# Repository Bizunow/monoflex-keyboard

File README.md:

# Monoflex keyboard

This repo contains case, plate, foam and PCB  design files for a Monoflex keyboard.

Case, plates and foam designed by me ([Bizunow](https://github.com/Bizunow)) and PCB designed by [keyten](https://github.com/KeyTen1).

Maintained by [Bizunow](https://github.com/Bizunow) & [ILWrites](https://github.com/pikeeb)

QMK Firmware source available on ILWrites' [Monoflex QMK branch](https://github.com/PiKeeb/qmk_firmware/tree/monoflex/keyboards/monoflex60)

Huge thanks to all, who helped me design this keyboard.

Licenced under WTFPL v2

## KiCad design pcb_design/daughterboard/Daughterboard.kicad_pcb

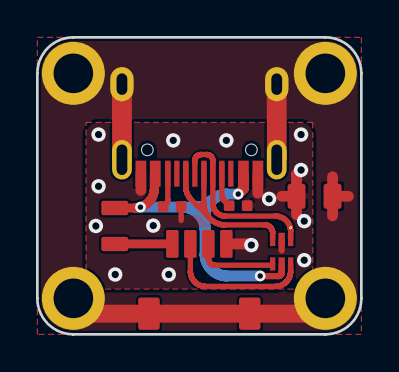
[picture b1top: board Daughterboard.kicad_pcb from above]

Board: 2 copper layers, 18.0 x 16.5 mm, 11 parts (0 on the bottom side), 10 nets.

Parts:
F1: 350mA; Fuse_0805
J1: TYPE-C-31-M12_13; TYPE-C-31-M-12
J2: JST SH; JST_SH
J3, J4, J5, J6: Conn_01x01; M2_MountingHole
L1: 60Ω@100MHz; L_0805
R1, R2: 5.1kΩ; R_0402
U2: USBLC6-2P6; SOT-666

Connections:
+5V: F1.2, J2.1
D+: J2.3, U2.4
D-: J2.2, U2.6
DBUS+: J1.A6, J1.B6, U2.3
DBUS-: J1.A7, J1.B7, U2.1
GND: J1.A1, J1.B1, J2.4, L1.2, R1.2, R2.1, U2.2
GNDPWR: J1.S, J2.5, J2.6, J3.1, J4.1, J5.1, J6.1, L1.1
unnamed: J1.A5, R1.1
unnamed: J1.B5, R2.2
VBUS: F1.1, J1.A4, J1.B4, U2.5

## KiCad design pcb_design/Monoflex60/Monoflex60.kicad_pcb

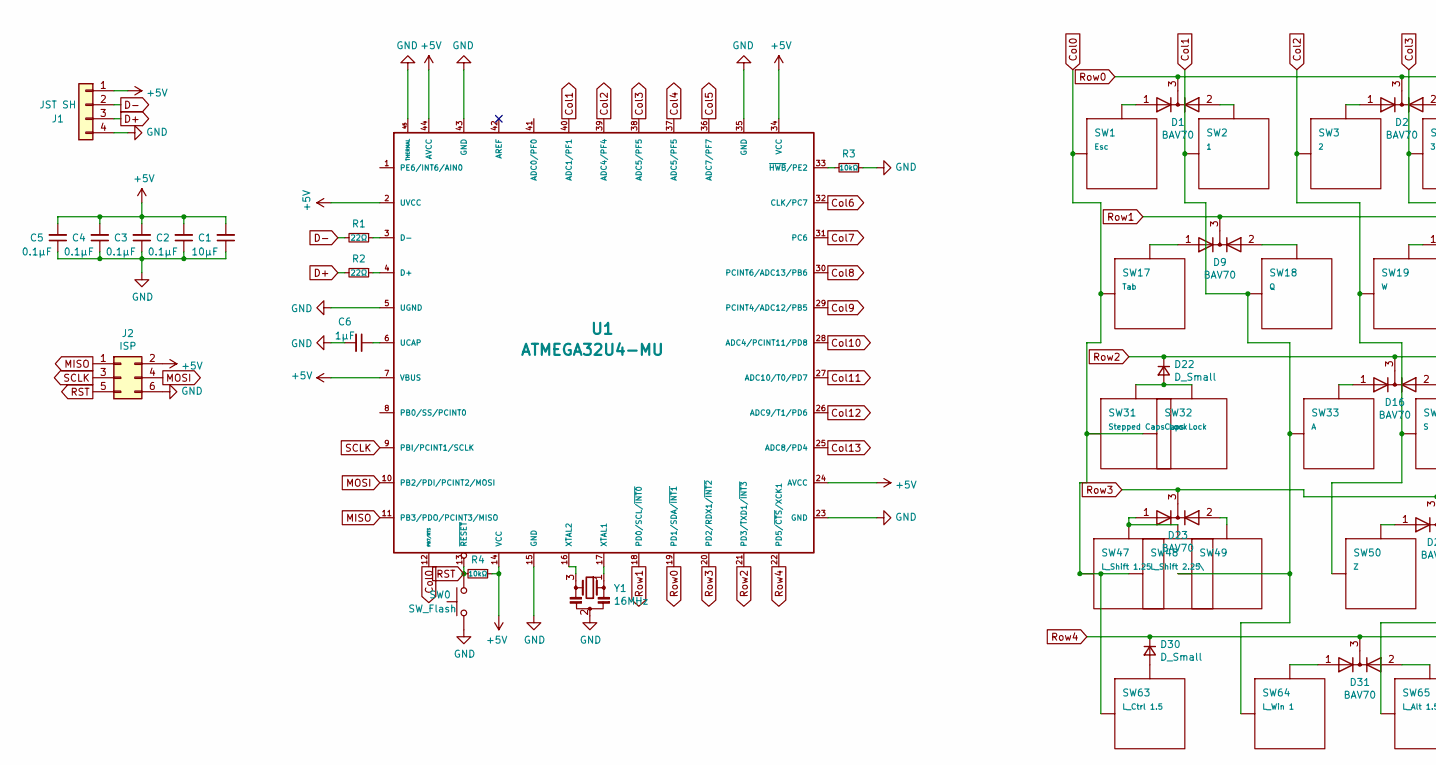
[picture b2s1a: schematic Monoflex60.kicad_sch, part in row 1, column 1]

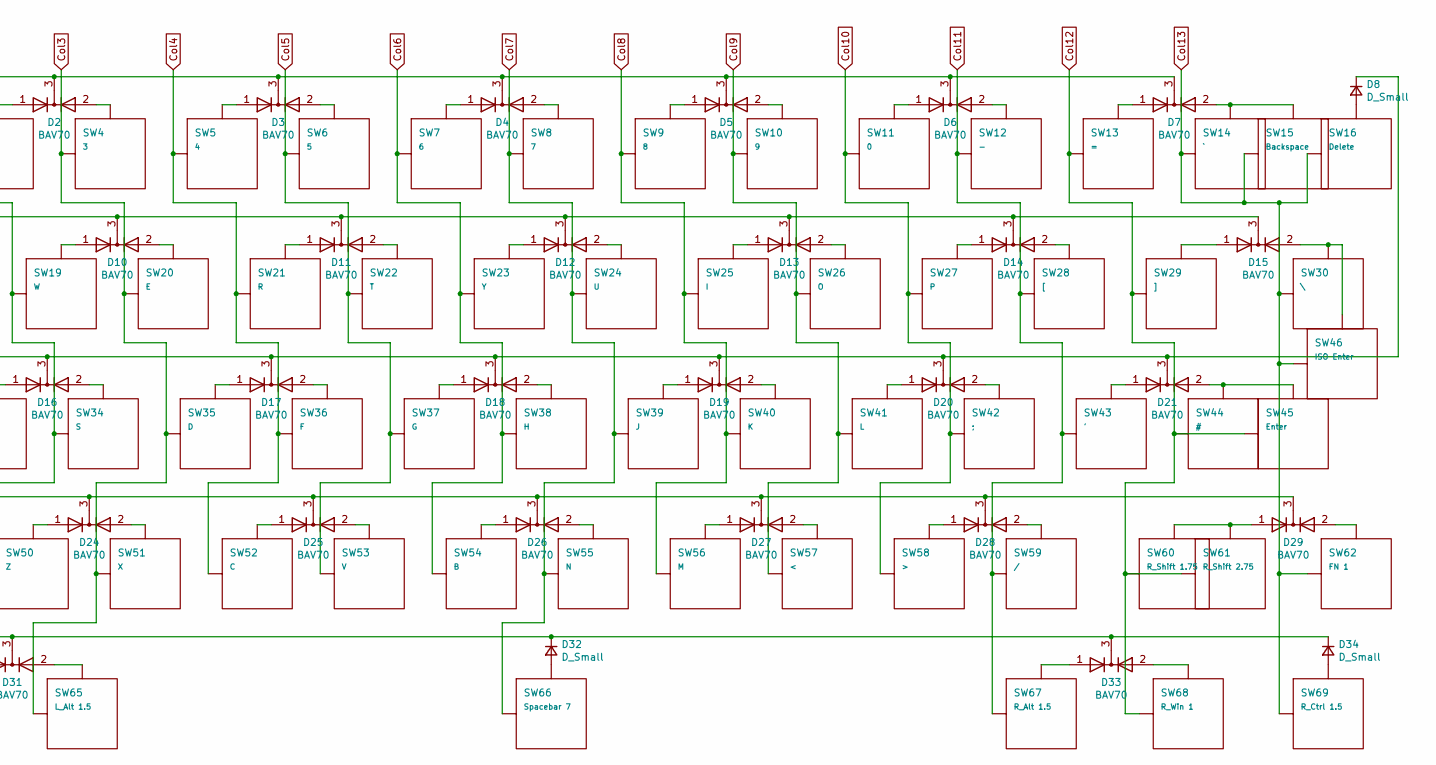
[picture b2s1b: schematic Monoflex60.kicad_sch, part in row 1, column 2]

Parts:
C1: 10μF; C_0402
C2, C3, C4, C5: 0.1μF; C_0402
C6: 1μF; C_0402
D1, D2, D3, D4, D5, D6, D7, D9, D10, D11, D12, D13, D14, D15, D16, D17, D18, D19, D20, D21, D23, D24, D25, D26, D27, D28, D29, D31, D33: BAV70; SOT-23
D8, D22, D30, D32, D34: D_Small; D_SOD-323
J1: JST SH; JST_SH
J2: ISP; AVR-ISP
R1, R2: 22Ω; R_0402
R3, R4: 10kΩ; R_0402
SW0: SW_Flash; ALPSALPINE-SKSV
SW1: Esc; 1U
SW2: 1; 1U
SW3: 2; 1U
SW4: 3; 1U
SW5: 4; 1U
SW6: 5; 1U
SW7: 6; 1U
SW8: 7; 1U
SW9: 8; 1U
SW10: 9; 1U
SW11: 0; 1U
SW12: -; 1U
SW13: =; 1U
SW14: `; 1U
SW15: Backspace; 2U
SW16: Delete; 1U
SW17: Tab; 1.5U
SW18: Q; 1U
SW19: W; 1U
SW20: E; 1U
SW21: R; 1U
SW22: T; 1U
SW23: Y; 1U
SW24: U; 1U
SW25: I; 1U
SW26: O; 1U
SW27: P; 1U
SW28: [; 1U
SW29: ]; 1U
SW30: \; 1.5U
SW31: Stepped Caps Lock; 1.75U-stepped_Caps_Lock
SW32: Caps Lock; 1.75U
SW33: A; 1U
SW34: S; 1U
SW35: D; 1U
SW36: F; 1U
SW37: G; 1U
SW38: H; 1U
SW39: J; 1U
SW40: K; 1U
SW41: L; 1U
SW42: ;; 1U
SW43: '; 1U
SW44: #; 1U
SW45: Enter; 2.25U
SW46: ISO Enter; ISO
SW47: L_Shift 1.25; 1.25U
SW48: L_Shift 2.25; 2.25U
SW49: \; 1U
SW50: Z; 1U
SW51: X; 1U
SW52: C; 1U
SW53: V; 1U
SW54: B; 1U
SW55: N; 1U
SW56: M; 1U
SW57: <; 1U
SW58: >; 1U
SW59: /; 1U
SW60: R_Shift 1.75; 1.75U
SW61: R_Shift 2.75; 2.75U
SW62: FN 1; 1U
SW63: L_Ctrl 1.5; 1.5U
SW64: L_Win 1; 1U
SW65: L_Alt 1.5; 1.5U
SW66: Spacebar 7; 7U-reverse_stabs
SW67: R_Alt 1.5; 1.5U
SW68: R_Win 1; 1U
SW69: R_Ctrl 1.5; 1.5U
U1: ATMEGA32U4-MU; QFN-44-SMT
Y1: 16MHz; Resonator_SMD_muRata_CSTxExxV-3Pin_3.0x1.1mm

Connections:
+5V: C1.2, C2.2, C3.2, C4.2, C5.2, J1.1, J2.2, R4.1, U1.2 (UVCC), U1.7 (VBUS), U1.14 (VCC), U1.24 (AVCC), U1.34 (VCC), U1.44 (AVCC)
Col0: SW1.1 (Col), SW17.1 (Col), SW31.1 (Col), SW32.1 (Col), SW47.1 (Col), SW48.1 (Col), SW63.1 (Col), U1.12 (PB7/RTS)
Col1: SW2.1 (Col), SW18.1 (Col), SW33.1 (Col), SW49.1 (Col), SW64.1 (Col), U1.40 (ADC1/PF1)
Col2: SW3.1 (Col), SW19.1 (Col), SW34.1 (Col), SW50.1 (Col), U1.39 (ADC4/PF4)
Col3: SW4.1 (Col), SW20.1 (Col), SW35.1 (Col), SW51.1 (Col), SW65.1 (Col), U1.38 (ADC5/PF5)
Col4: SW5.1 (Col), SW21.1 (Col), SW36.1 (Col), SW52.1 (Col), U1.37 (ADC5/PF5)
Col5: SW6.1 (Col), SW22.1 (Col), SW37.1 (Col), SW53.1 (Col), U1.36 (ADC7/PF7)
Col6: SW7.1 (Col), SW23.1 (Col), SW38.1 (Col), SW54.1 (Col), U1.32 (CLK/PC7)
Col7: SW8.1 (Col), SW24.1 (Col), SW39.1 (Col), SW55.1 (Col), SW66.1 (Col), U1.31 (PC6)
Col8: SW9.1 (Col), SW25.1 (Col), SW40.1 (Col), SW56.1 (Col), U1.30 (PCINT6/ADC13/PB6)
Col9: SW10.1 (Col), SW26.1 (Col), SW41.1 (Col), SW57.1 (Col), U1.29 (PCINT4/ADC12/PB5)
Col10: SW11.1 (Col), SW27.1 (Col), SW42.1 (Col), SW58.1 (Col), U1.28 (ADC4/PCINT11/PD8)
Col11: SW12.1 (Col), SW28.1 (Col), SW43.1 (Col), SW59.1 (Col), SW67.1 (Col), U1.27 (ADC10/T0/PD7)
Col12: SW13.1 (Col), SW29.1 (Col), SW44.1 (Col), SW45.1 (Col), SW60.1 (Col), SW61.1 (Col), SW68.1 (Col), U1.26 (ADC9/T1/PD6)
Col13: SW14.1 (Col), SW15.1 (Col), SW16.1 (Col), SW30.1 (Col), SW46.1 (Col), SW62.1 (Col), SW69.1 (Col), U1.25 (ADC8/PD4)
D+: J1.3, R2.2
D-: J1.2, R1.2
GND: C1.1, C2.1, C3.1, C4.1, C5.1, C6.2, J1.4, J2.6, R3.1, SW0.1, U1.5 (UGND), U1.15 (GND), U1.23 (GND), U1.35 (GND), U1.43 (GND), U1.45 (THERMAL), Y1.2
MISO: J2.1, U1.11 (PB3/PDO/PCINT3/MISO)
MOSI: J2.4, U1.10 (PB2/PDI/PCINT2/MOSI)
unnamed: C6.1, U1.6 (UCAP)
unnamed: D1.1 (A), SW1.2 (Row)
unnamed: D1.2 (A), SW2.2 (Row)
unnamed: D2.1 (A), SW3.2 (Row)
unnamed: D2.2 (A), SW4.2 (Row)
unnamed: D3.1 (A), SW5.2 (Row)
unnamed: D3.2 (A), SW6.2 (Row)
unnamed: D4.1 (A), SW7.2 (Row)
unnamed: D4.2 (A), SW8.2 (Row)
unnamed: D5.1 (A), SW9.2 (Row)
unnamed: D5.2 (A), SW10.2 (Row)
unnamed: D6.1 (A), SW11.2 (Row)
unnamed: D6.2 (A), SW12.2 (Row)
unnamed: D7.1 (A), SW13.2 (Row)
unnamed: D7.2 (A), SW14.2 (Row), SW15.2 (Row)
unnamed: D8.2 (A), SW16.2 (Row)
unnamed: D9.1 (A), SW17.2 (Row)
unnamed: D9.2 (A), SW18.2 (Row)
unnamed: D10.1 (A), SW19.2 (Row)
unnamed: D10.2 (A), SW20.2 (Row)
unnamed: D11.1 (A), SW21.2 (Row)
unnamed: D11.2 (A), SW22.2 (Row)
unnamed: D12.1 (A), SW23.2 (Row)
unnamed: D12.2 (A), SW24.2 (Row)
unnamed: D13.1 (A), SW25.2 (Row)
unnamed: D13.2 (A), SW26.2 (Row)
unnamed: D14.1 (A), SW27.2 (Row)
unnamed: D14.2 (A), SW28.2 (Row)
unnamed: D15.1 (A), SW29.2 (Row)
unnamed: D15.2 (A), SW30.2 (Row), SW46.2 (Row)
unnamed: D16.1 (A), SW33.2 (Row)
unnamed: D16.2 (A), SW34.2 (Row)
unnamed: D17.1 (A), SW35.2 (Row)
unnamed: D17.2 (A), SW36.2 (Row)
unnamed: D18.1 (A), SW37.2 (Row)
unnamed: D18.2 (A), SW38.2 (Row)
unnamed: D19.1 (A), SW39.2 (Row)
unnamed: D19.2 (A), SW40.2 (Row)
unnamed: D20.1 (A), SW41.2 (Row)
unnamed: D20.2 (A), SW42.2 (Row)
unnamed: D21.1 (A), SW43.2 (Row)
unnamed: D21.2 (A), SW44.2 (Row), SW45.2 (Row)
unnamed: D22.2 (A), SW31.2 (Row), SW32.2 (Row)
unnamed: D23.1 (A), SW47.2 (Row), SW48.2 (Row)
unnamed: D23.2 (A), SW49.2 (Row)
unnamed: D24.1 (A), SW50.2 (Row)
unnamed: D24.2 (A), SW51.2 (Row)
unnamed: D25.1 (A), SW52.2 (Row)
unnamed: D25.2 (A), SW53.2 (Row)
unnamed: D26.1 (A), SW54.2 (Row)
unnamed: D26.2 (A), SW55.2 (Row)
unnamed: D27.1 (A), SW56.2 (Row)
unnamed: D27.2 (A), SW57.2 (Row)
unnamed: D28.1 (A), SW58.2 (Row)
unnamed: D28.2 (A), SW59.2 (Row)
unnamed: D29.1 (A), SW60.2 (Row), SW61.2 (Row)
unnamed: D29.2 (A), SW62.2 (Row)
unnamed: D30.2 (A), SW63.2 (Row)
unnamed: D31.1 (A), SW64.2 (Row)
unnamed: D31.2 (A), SW65.2 (Row)
unnamed: D32.2 (A), SW66.2 (Row)
unnamed: D33.1 (A), SW67.2 (Row)
unnamed: D33.2 (A), SW68.2 (Row)
unnamed: D34.2 (A), SW69.2 (Row)
unnamed: R1.1, U1.3 (D-)
unnamed: R2.1, U1.4 (D+)
unnamed: R3.2, U1.33 (~HWB/PE2)
unnamed: U1.16 (XTAL2), Y1.3
unnamed: U1.17 (XTAL1), Y1.1
RST: J2.5, R4.2, SW0.2, U1.13 (~RESET)
Row0: D1.3 (K), D2.3 (K), D3.3 (K), D4.3 (K), D5.3 (K), D6.3 (K), D7.3 (K), U1.19 (PD1/SDA/~INT1)
Row1: D9.3 (K), D10.3 (K), D11.3 (K), D12.3 (K), D13.3 (K), D14.3 (K), D15.3 (K), U1.18 (PD0/SCL/~INT0)
Row2: D8.1 (K), D16.3 (K), D17.3 (K), D18.3 (K), D19.3 (K), D20.3 (K), D21.3 (K), D22.1 (K), U1.21 (PD3/TXD1/~INT3)
Row3: D23.3 (K), D24.3 (K), D25.3 (K), D26.3 (K), D27.3 (K), D28.3 (K), D29.3 (K), U1.20 (PD2/RDX1/~INT2)
Row4: D30.1 (K), D31.3 (K), D32.1 (K), D33.3 (K), D34.1 (K), U1.22 (PD5/~CTS/XCK1)
SCLK: J2.3, U1.9 (PBI/PCINT1/SCLK)

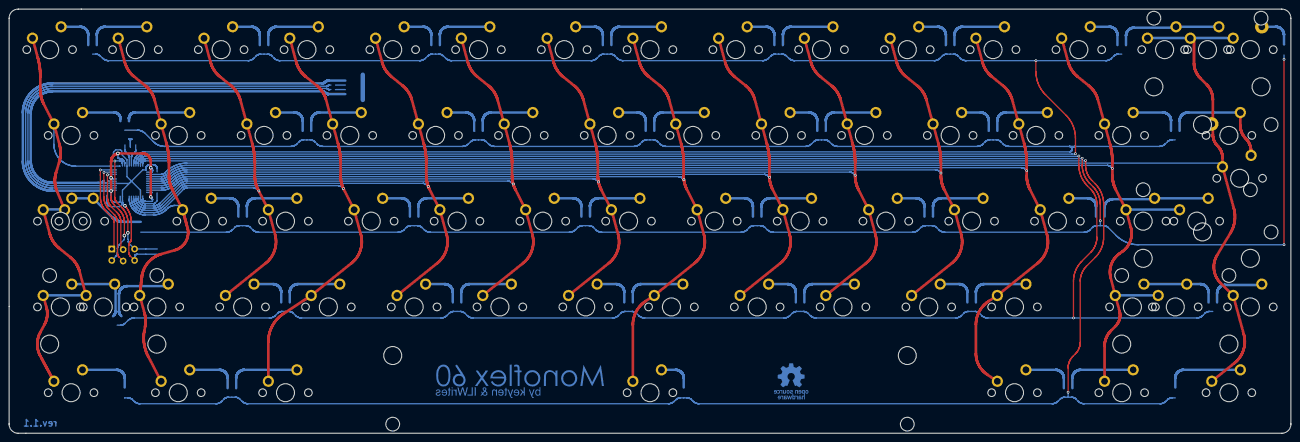
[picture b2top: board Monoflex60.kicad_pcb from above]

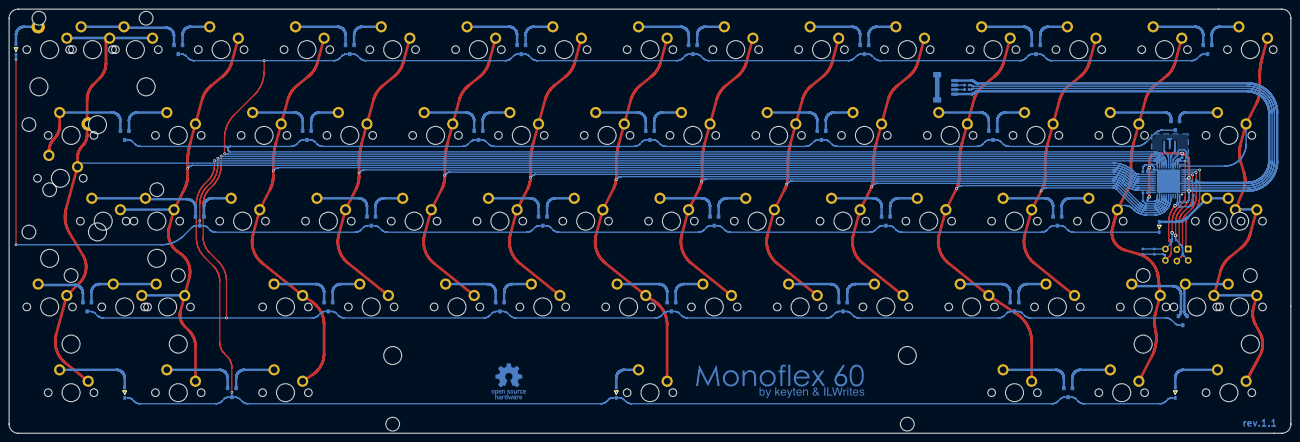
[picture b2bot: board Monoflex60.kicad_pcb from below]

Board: 2 copper layers, 284.7 x 94.2 mm, 118 parts (49 on the bottom side), 96 nets.

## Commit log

2021-12-04 kekw
2021-12-06 overhaul&cleanup
2021-12-06 Added daughterboard PCB design
2021-12-06 Changed readme & added the licence
